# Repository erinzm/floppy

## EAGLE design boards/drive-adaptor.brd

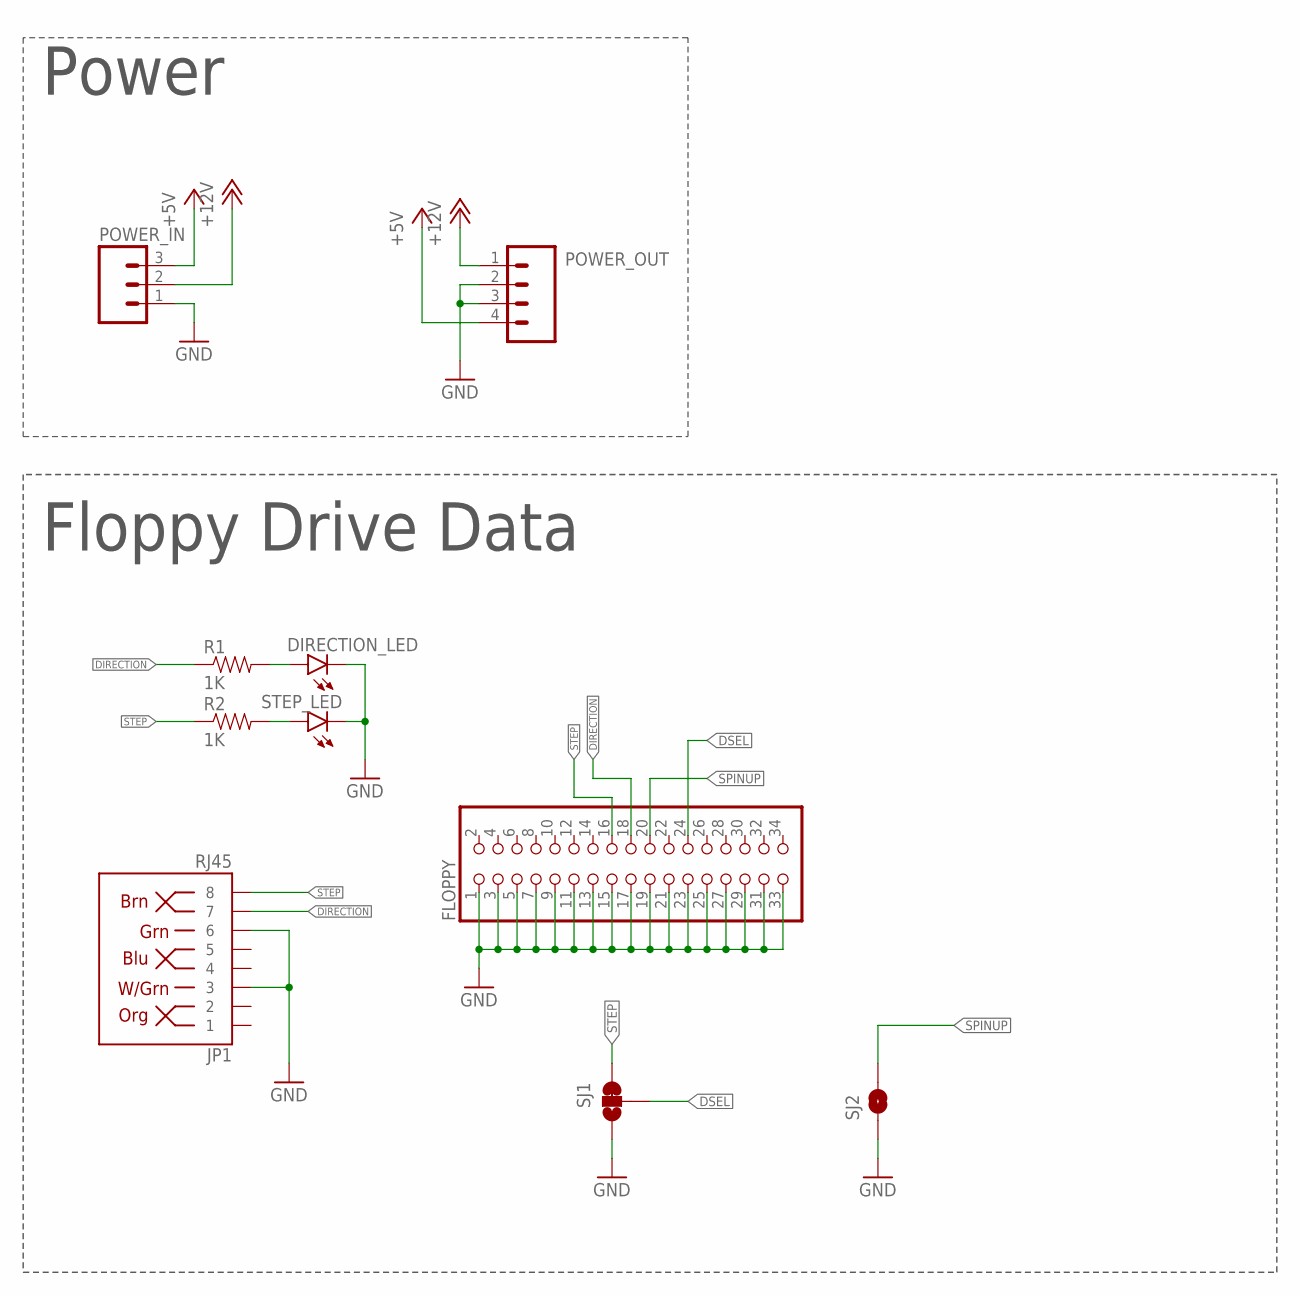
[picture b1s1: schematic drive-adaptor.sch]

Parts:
DIRECTION_LED: LED1206; LED-1206
FLOPPY: PINHD-2X17; 2X17
JP1: RJ45; RJ45-8
POWER_IN: M03-SCREW-5MM; SCREWTERMINAL-5MM-3
POWER_OUT: M04LONGPADS; 1X04_LONGPADS
R1, R2: 1K; 0603-RES
SJ1: JUMPER-PAD-3-2OF3_NC_BY_TRACE_SMALL; PAD-JUMPER-3-2OF3_NC_BY_TRACE_YES_SILK_FULL_BOX
SJ2: JUMPER-PAD-2-NOYES_SILK; PAD-JUMPER-2-NO_YES_SILK
STEP_LED: LED1206; LED-1206

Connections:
+5V: POWER_IN.3, POWER_OUT.4
+12V: POWER_IN.2, POWER_OUT.1
DIRECTION: FLOPPY.18, JP1.7, R1.1
DSEL: FLOPPY.24, SJ1.2
GND: DIRECTION_LED.C, FLOPPY.1, FLOPPY.3, FLOPPY.5, FLOPPY.7, FLOPPY.9, FLOPPY.11, FLOPPY.13, FLOPPY.15, FLOPPY.17, FLOPPY.19, FLOPPY.21, FLOPPY.23, FLOPPY.25, FLOPPY.27, FLOPPY.29, FLOPPY.31, FLOPPY.33, JP1.3, JP1.6, POWER_IN.1, POWER_OUT.2, POWER_OUT.3, SJ1.1, SJ2.1, STEP_LED.C
unnamed: DIRECTION_LED.A, R1.2
unnamed: R2.2, STEP_LED.A
SPINUP: FLOPPY.20, SJ2.2
STEP: FLOPPY.16, JP1.8, R2.1, SJ1.3

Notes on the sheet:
Power
Floppy Drive Data

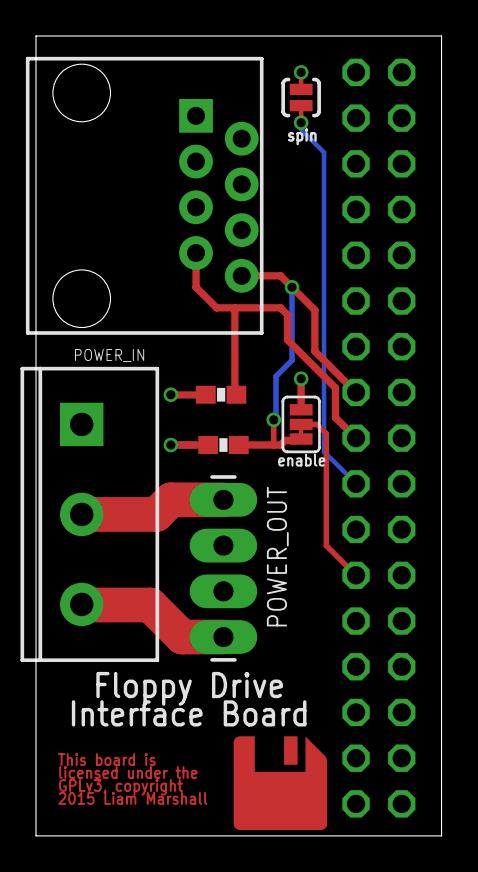
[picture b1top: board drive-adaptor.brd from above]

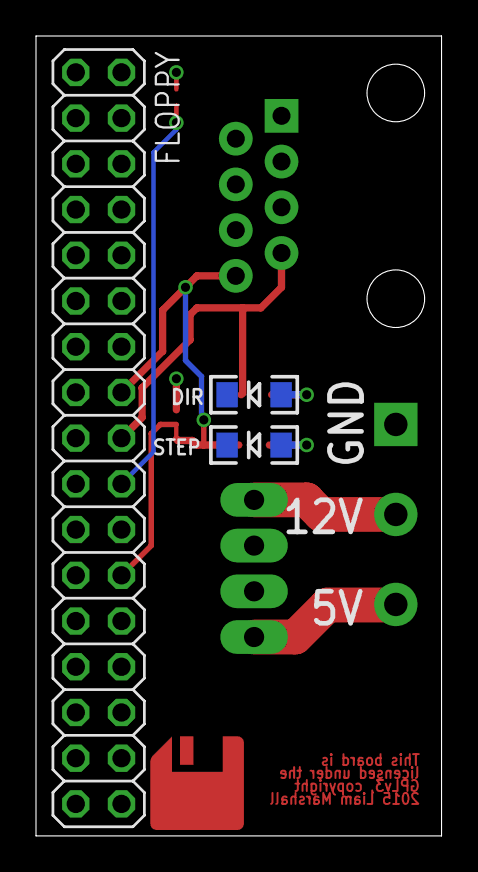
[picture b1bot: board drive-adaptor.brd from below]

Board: 2 copper layers, 22.5 x 44.4 mm, 10 parts (3 on the bottom side), 9 nets.

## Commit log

2015-05-24 Remove Floppy.ino
2015-05-24 codegen script
2015-05-26 EAGLE gitignore
2015-05-26 Board dump

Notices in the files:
boards/drive-adaptor.brd:
licensed under the
GPLv3, copyright
parts and their libraries:
SparkFun-Connectors: Licensing: Creative Commons ShareAlike 4.0 International - https://creativecommons.org/licenses/by-sa/4.0
